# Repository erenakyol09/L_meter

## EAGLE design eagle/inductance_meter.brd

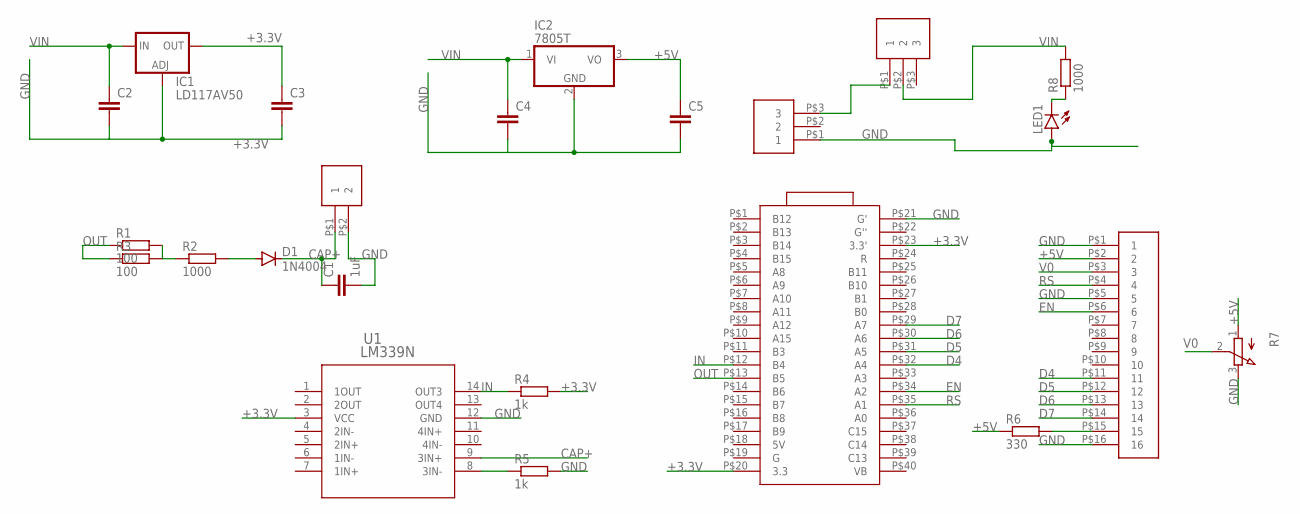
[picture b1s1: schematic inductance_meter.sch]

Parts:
C1: 1uF; C050-075X075
C2, C3, C4, C5: C-EU025-030X050; C025-030X050
D1: 1N4004; DO41-10
IC1: LD117AV50; TO220L1
IC2: 7805T; TO220H
LED1: TLLR4400; LED3MM
R1, R3: 100; P0817/22
R2, R8: 1000; P0817/22
R4, R5: 1k; P0817/22
R6: 330; 0617/17
R7: 3RP/1610N
U1: LM339N; PDIP14_6P60X19P69_ONS
U$2: HEADER_16; HEADER_16_FOOT
U$3: BLUE_PILL_EA; BLUE_PILL_FOOT
U$5: HEADER_2; HEADER_2_FOOT
U$7, U$9: HEADER_3; HEADER_3_FOOT

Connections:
+3.3V: C3.1, IC1.2 (OUT), R4.2, U1.3 (VCC), U$3.P$20 (3.3), U$3.P$23 (3.3')
+5V: C5.1, IC2.3 (VO), R6.1, R7.1 (A), U$2.P$2 (2)
CAP+: C1.1, D1.C, U1.9 (3IN+), U$5.P$1 (1)
D4: U$2.P$11 (11), U$3.P$32 (A4)
D5: U$2.P$12 (12), U$3.P$31 (A5)
D6: U$2.P$13 (13), U$3.P$30 (A6)
D7: U$2.P$14 (14), U$3.P$29 (A7)
EN: U$2.P$6 (6), U$3.P$34 (A2)
GND: C1.2, C2.2, C3.2, C4.2, C5.2, IC1.1 (ADJ), IC2.2 (GND), LED1.A, R5.2, R7.3 (E), U1.12 (GND), U$2.P$1 (1), U$2.P$5 (5), U$2.P$16 (16), U$3.P$21 (G'), U$5.P$2 (2), U$9.P$1 (1)
IN: R4.1, U1.14 (OUT3), U$3.P$12 (B4)
unnamed: R6.2, U$2.P$15 (15)
unnamed: R5.1, U1.8 (3IN-)
unnamed: R1.2, R2.1, R3.2
unnamed: D1.A, R2.2
unnamed: LED1.K (C), R8.1
unnamed: U$7.P$1 (1), U$9.P$3 (3)
OUT: R1.1, R3.1, U$3.P$13 (B5)
RS: U$2.P$4 (4), U$3.P$35 (A1)
V0: R7.2 (S), U$2.P$3 (3)
VIN: C2.1, C4.1, IC1.3 (IN), IC2.1 (VI), R8.2, U$7.P$2 (2)

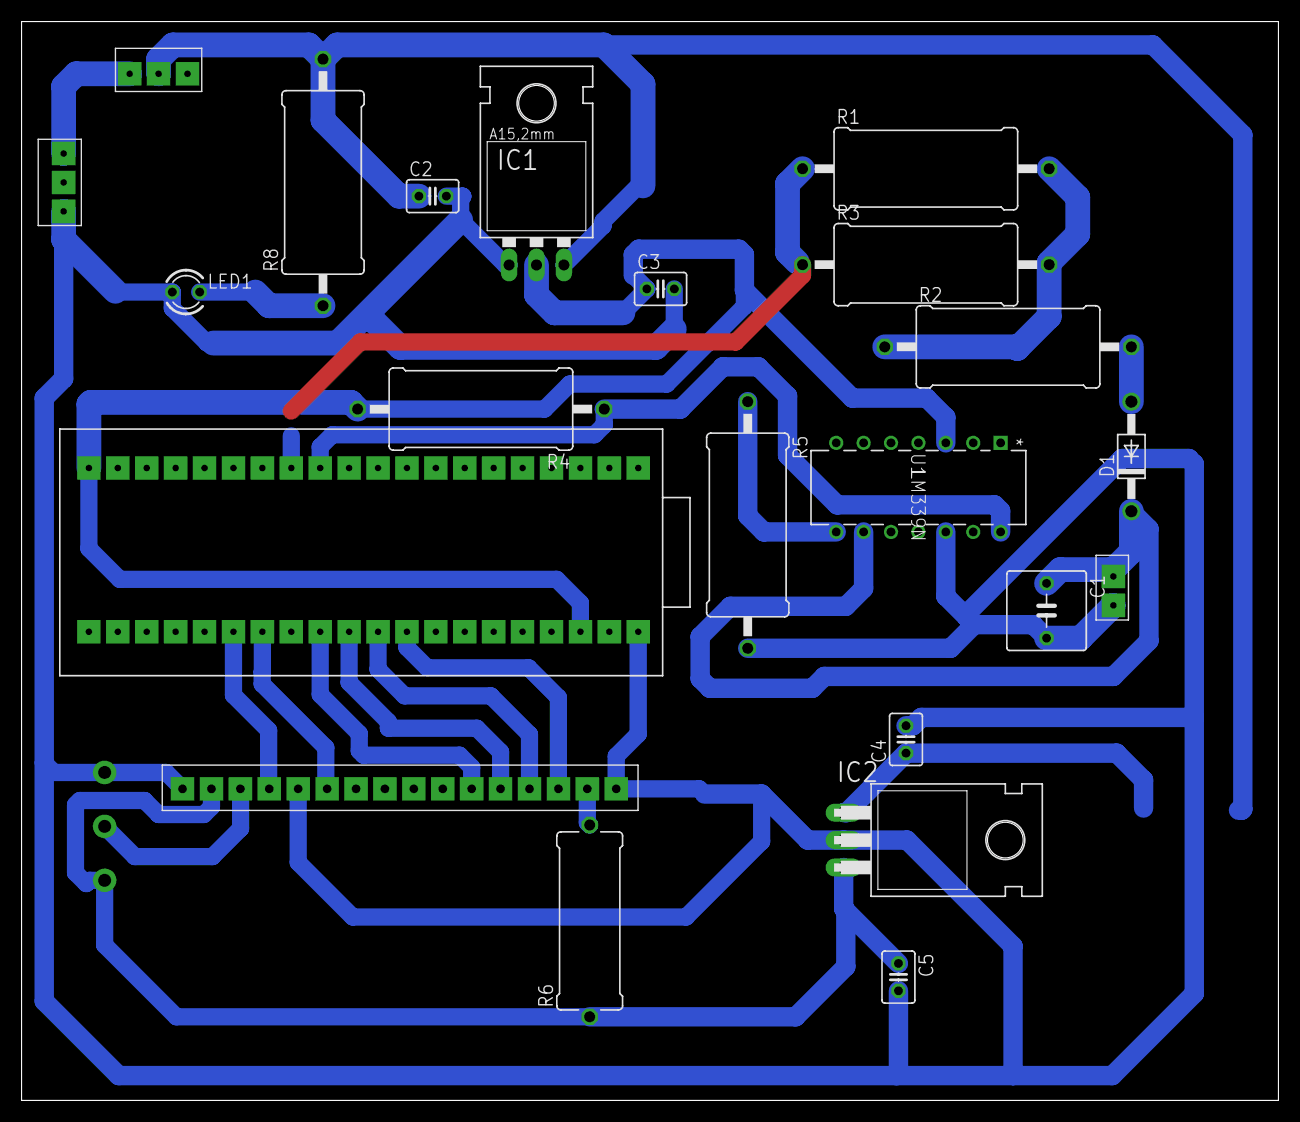
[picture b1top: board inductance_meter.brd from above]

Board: 2 copper layers, 116.5 x 100.0 mm, 23 parts (1 on the bottom side), 20 nets.

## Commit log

2020-08-14 lc_m_v1

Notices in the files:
parts and their libraries:
COPYRIGHT: Copyright (C) 2018 Accelerated Designs. All rights reserved
